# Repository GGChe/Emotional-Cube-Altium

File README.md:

# Emotional-Cube-Altium
Emotional Cube Design at Polythecnic University of Madrid redesigned and translated to Altium

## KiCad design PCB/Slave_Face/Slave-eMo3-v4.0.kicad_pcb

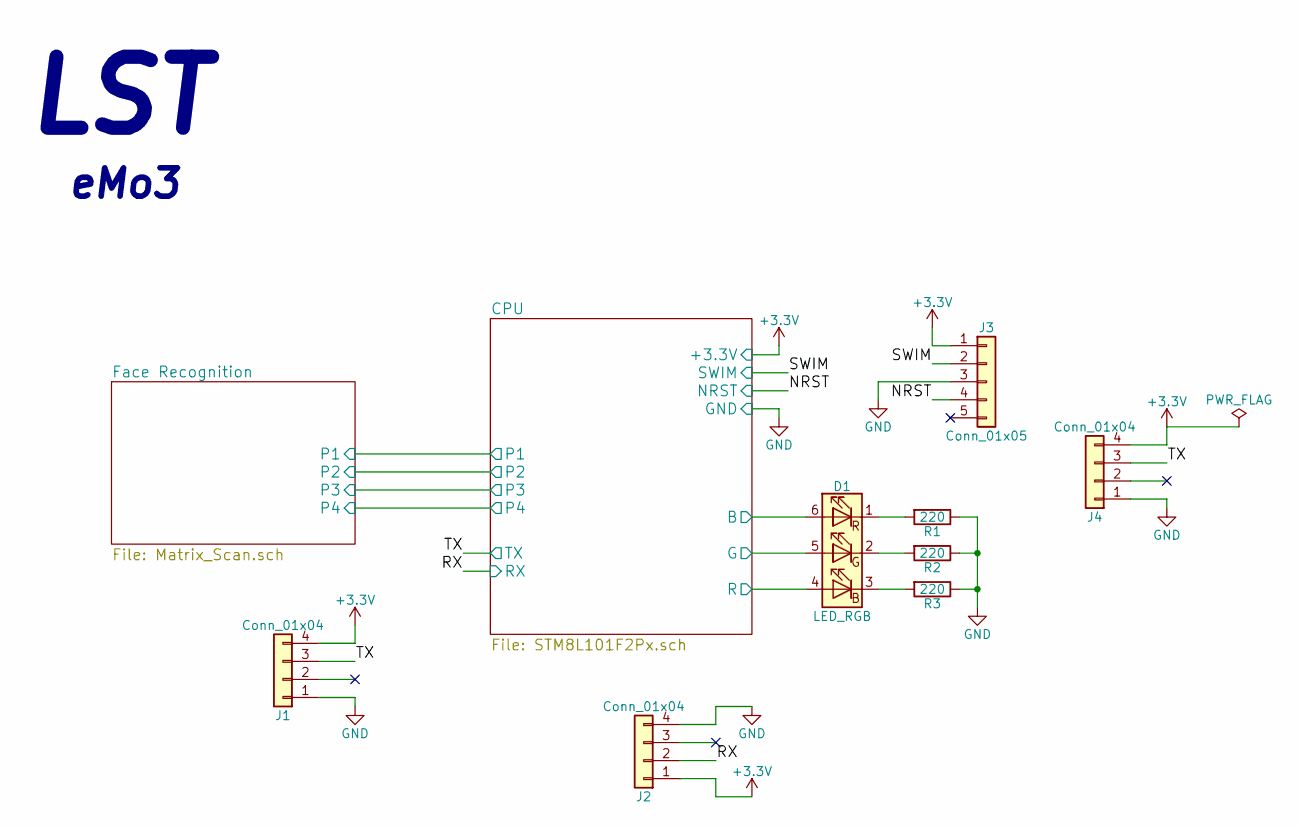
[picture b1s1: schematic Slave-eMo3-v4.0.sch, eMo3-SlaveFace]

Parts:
D1: LED_RGB; LED_RGB_PLCC-6
J1, J2, J4: Conn_01x04; 200528-0040
J3: Conn_01x05; Pin_Header_Straight_1x05_Pitch2.54mm
R1, R2, R3: 220; R_0402

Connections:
+3V3: J1.4, J2.1, J3.1, J4.4; also elsewhere on the board
/CPU/B: D1.6 (RA); also elsewhere on the board
/CPU/G: D1.5 (GA); also elsewhere on the board
/CPU/R: D1.4 (BA); also elsewhere on the board
/NRST: J3.4; also elsewhere on the board
/RX: J2.2; also elsewhere on the board
/SWIM: J3.2; also elsewhere on the board
/TX: J1.3, J4.3; also elsewhere on the board
GND: J1.1, J2.4, J3.3, J4.1, R1.1, R2.1, R3.1; also elsewhere on the board
unnamed: D1.1 (RK), R1.2
unnamed: D1.2 (GK), R2.2
unnamed: D1.3 (BK), R3.2

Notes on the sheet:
LST
eMo3

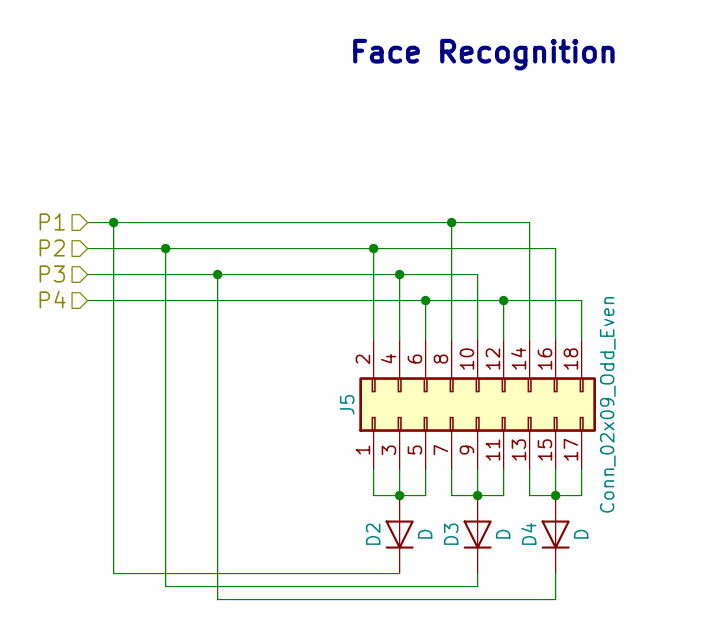
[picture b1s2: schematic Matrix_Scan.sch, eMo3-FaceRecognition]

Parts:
D2, D3, D4: D; D_0603
J5: Conn_02x09_Odd_Even; Pin_Header_Straight_2x09_Pitch2.54mm

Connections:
/CPU/P1: D2.1 (K), J5.8, J5.14; also elsewhere on the board
/CPU/P2: D3.1 (K), J5.2, J5.16; also elsewhere on the board
/CPU/P3: D4.1 (K), J5.4, J5.10; also elsewhere on the board
/CPU/P4: J5.6, J5.12, J5.18; also elsewhere on the board
unnamed: D2.2 (A), J5.1, J5.3, J5.5
unnamed: D3.2 (A), J5.7, J5.9, J5.11
unnamed: D4.2 (A), J5.13, J5.15, J5.17

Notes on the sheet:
Face Recognition

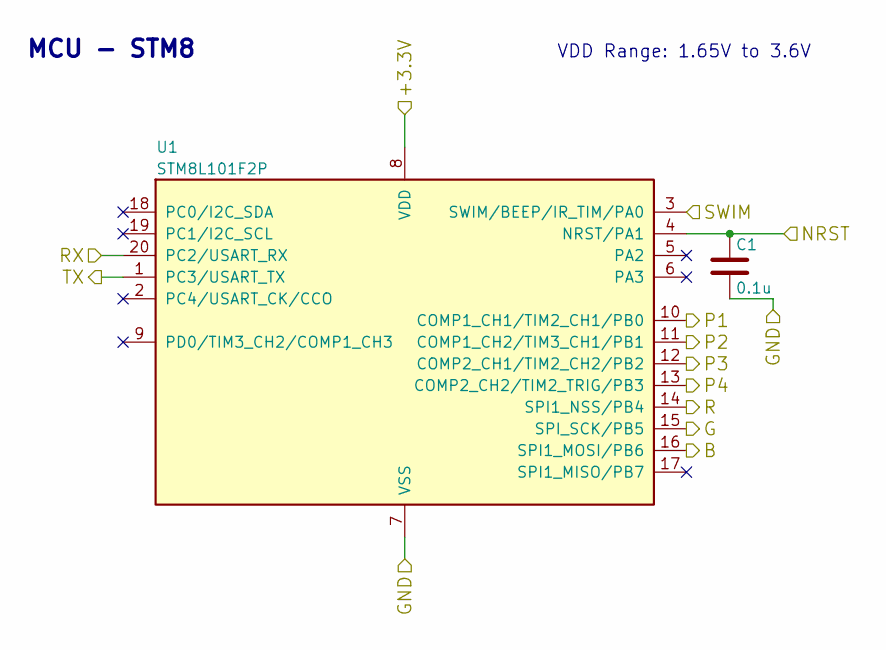
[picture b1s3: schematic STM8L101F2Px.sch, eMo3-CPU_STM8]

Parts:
C1: 0.1u; C_0402
U1: STM8L101F2P; TSSOP-20_4.4x6.5mm_Pitch0.65mm

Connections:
+3V3: U1.8 (VDD); also elsewhere on the board
/CPU/B: U1.16 (SPI1_MOSI/PB6); also elsewhere on the board
/CPU/G: U1.15 (SPI_SCK/PB5); also elsewhere on the board
/CPU/P1: U1.10 (COMP1_CH1/TIM2_CH1/PB0); also elsewhere on the board
/CPU/P2: U1.11 (COMP1_CH2/TIM3_CH1/PB1); also elsewhere on the board
/CPU/P3: U1.12 (COMP2_CH1/TIM2_CH2/PB2); also elsewhere on the board
/CPU/P4: U1.13 (COMP2_CH2/TIM2_TRIG/PB3); also elsewhere on the board
/CPU/R: U1.14 (SPI1_NSS/PB4); also elsewhere on the board
/NRST: C1.1, U1.4 (NRST/PA1); also elsewhere on the board
/RX: U1.20 (PC2/USART_RX); also elsewhere on the board
/SWIM: U1.3 (SWIM/BEEP/IR_TIM/PA0); also elsewhere on the board
/TX: U1.1 (PC3/USART_TX); also elsewhere on the board
GND: C1.2, U1.7 (VSS); also elsewhere on the board

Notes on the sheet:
MCU - STM8
VDD Range: 1.65V to 3.6V

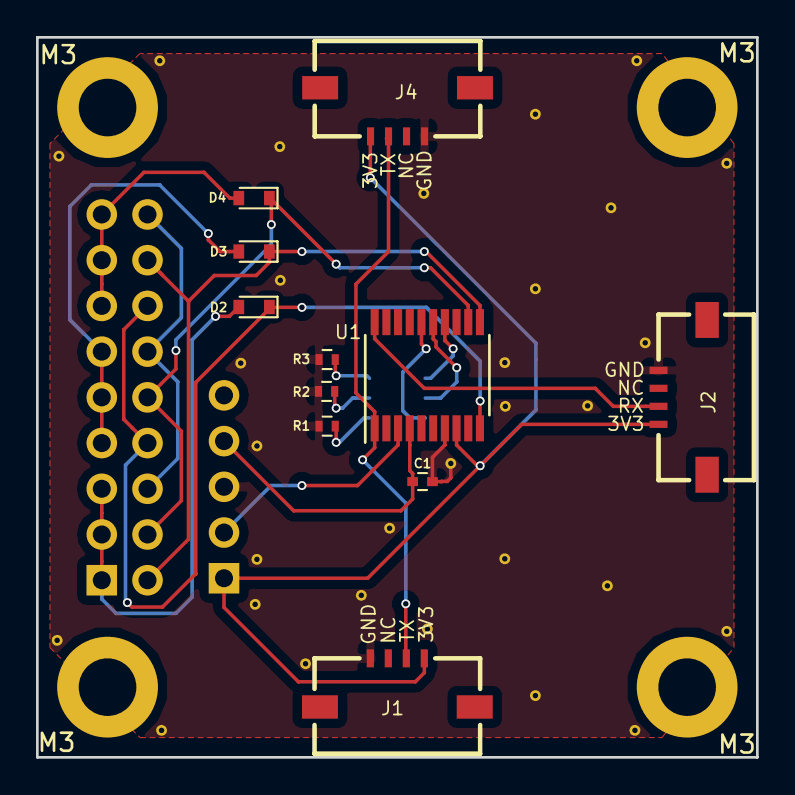
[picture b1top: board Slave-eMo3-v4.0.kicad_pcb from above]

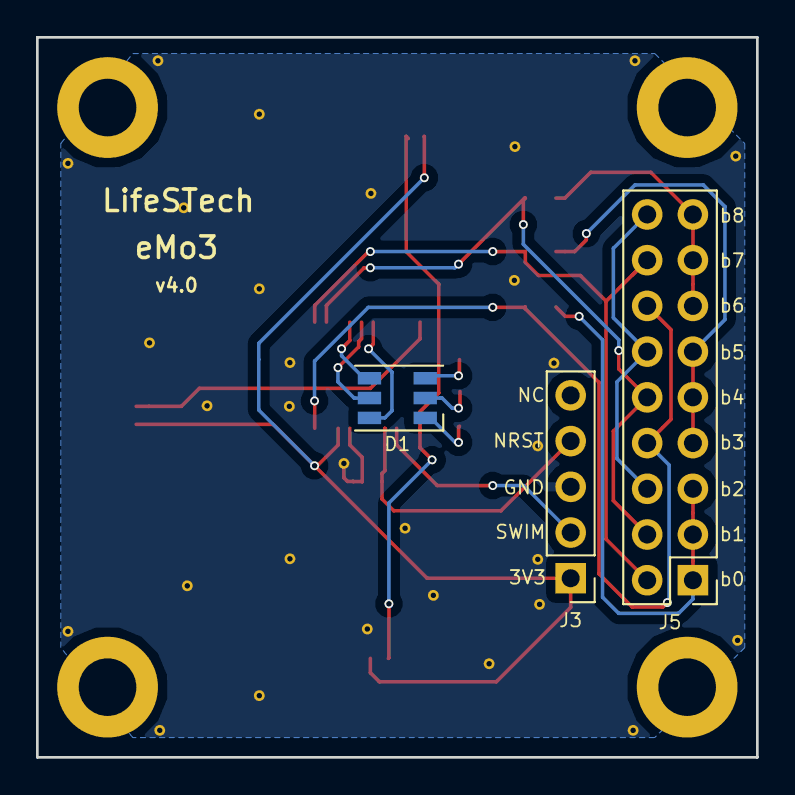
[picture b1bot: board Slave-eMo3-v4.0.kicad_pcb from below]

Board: 2 copper layers, 40.0 x 40.0 mm, 18 parts (3 on the bottom side), 19 nets.

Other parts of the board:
M3, M3#2, M3#3, M3#4: MountingHole_3.2mm_M3_DIN965_Pad
